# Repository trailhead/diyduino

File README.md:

# diyduino
Open source Arduino-compaitible using only through hole soldering

USB interface is provided by either a 6 pin FTDI, or CP2102 style adapter.  Pinouts are provided for each.

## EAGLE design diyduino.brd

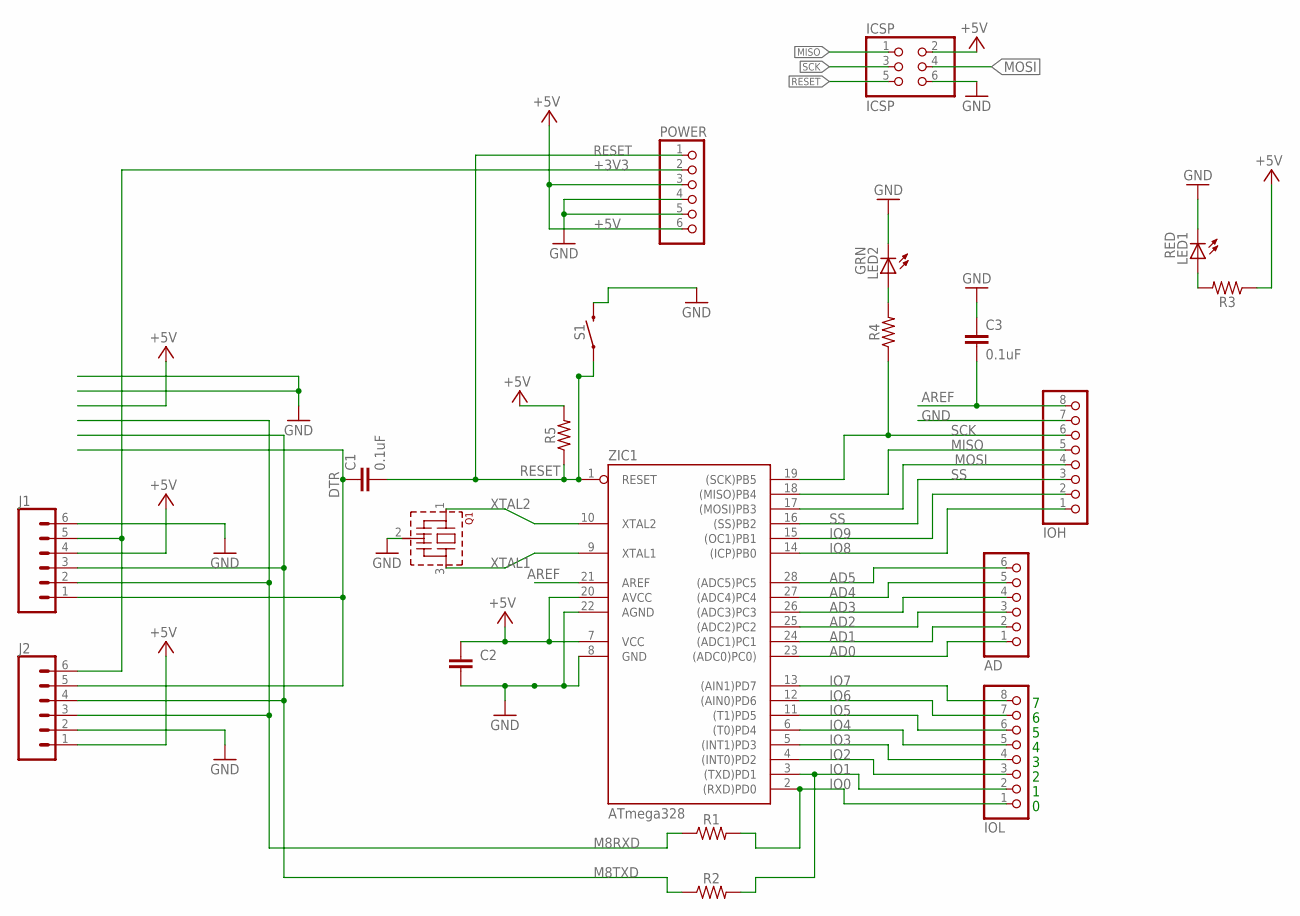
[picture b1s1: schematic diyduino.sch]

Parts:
AD: PINHD-1X6; 1X06
C1, C2, C3: 0.1uF; C2.5-2
ICSP: ICSP; 2X03
IOH: PINHD-1X8; 1X08
IOL: PINHD-1X8; 1X08
J1, J2: CONN_06SILK_FEMALE_PTH; 1X06
LED1: RED; LED3MM
LED2: GRN; LED3MM
POWER: PINHD-1X6; 1X06
Q1: CSTLS_X
R1, R2, R3, R4, R5: AXIAL-0.3
S1: MOMENTARY-SWITCH-SPST-PTH-6.0MM; TACTILE_SWITCH_PTH_6.0MM
ZIC1: ATmega328; DIL28-3

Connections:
+3V3: J1.5, J2.6, POWER.2
+5V: C2.2, ICSP.2, J1.4, J2.1, POWER.3, POWER.6, R3.P$1 (1), R5.P$2 (2), ZIC1.7 (VCC), ZIC1.20 (AVCC)
AD0: AD.1, ZIC1.23 ((ADC0)PC0))
AD1: AD.2, ZIC1.24 ((ADC1)PC1)
AD2: AD.3, ZIC1.25 ((ADC2)PC2)
AD3: AD.4, ZIC1.26 ((ADC3)PC3)
AD4: AD.5, ZIC1.27 ((ADC4)PC4)
AD5: AD.6, ZIC1.28 ((ADC5)PC5)
AREF: C3.2, IOH.8, ZIC1.21 (AREF)
DTR: C1.1, J1.1, J2.5
GND: C2.1, C3.1, ICSP.6, IOH.7, J1.6, J2.2, LED1.K (C), LED2.K (C), POWER.4, POWER.5, Q1.2 (VSS), S1.3 (2), ZIC1.8 (GND), ZIC1.22 (AGND)
IO0: IOL.1, R1.P$2 (2), ZIC1.2 ((RXD)PD0)
IO1: IOL.2, R2.P$2 (2), ZIC1.3 ((TXD)PD1)
IO2: IOL.3, ZIC1.4 ((INT0)PD2)
IO3: IOL.4, ZIC1.5 ((INT1)PD3)
IO4: IOL.5, ZIC1.6 ((T0)PD4)
IO5: IOL.6, ZIC1.11 ((T1)PD5)
IO6: IOL.7, ZIC1.12 ((AIN0)PD6)
IO7: IOL.8, ZIC1.13 ((AIN1)PD7)
IO8: IOH.1, ZIC1.14 ((ICP)PB0)
IO9: IOH.2, ZIC1.15 ((OC1)PB1)
M8RXD: J1.2, J2.3, R1.P$1 (1)
M8TXD: J1.3, J2.4, R2.P$1 (1)
MISO: ICSP.1, IOH.5, ZIC1.18 ((MISO)PB4)
MOSI: ICSP.4, IOH.4, ZIC1.17 ((MOSI)PB3)
unnamed: LED2.A, R4.P$2 (2)
unnamed: LED1.A, R3.P$2 (2)
RESET: C1.2, ICSP.5, POWER.1, R5.P$1 (1), S1.1, ZIC1.1 (RESET)
SCK: ICSP.3, IOH.6, R4.P$1 (1), ZIC1.19 ((SCK)PB5)
SS: IOH.3, ZIC1.16 ((SS)PB2)
XTAL1: Q1.3, ZIC1.9 (XTAL1)
XTAL2: Q1.1, ZIC1.10 (XTAL2)

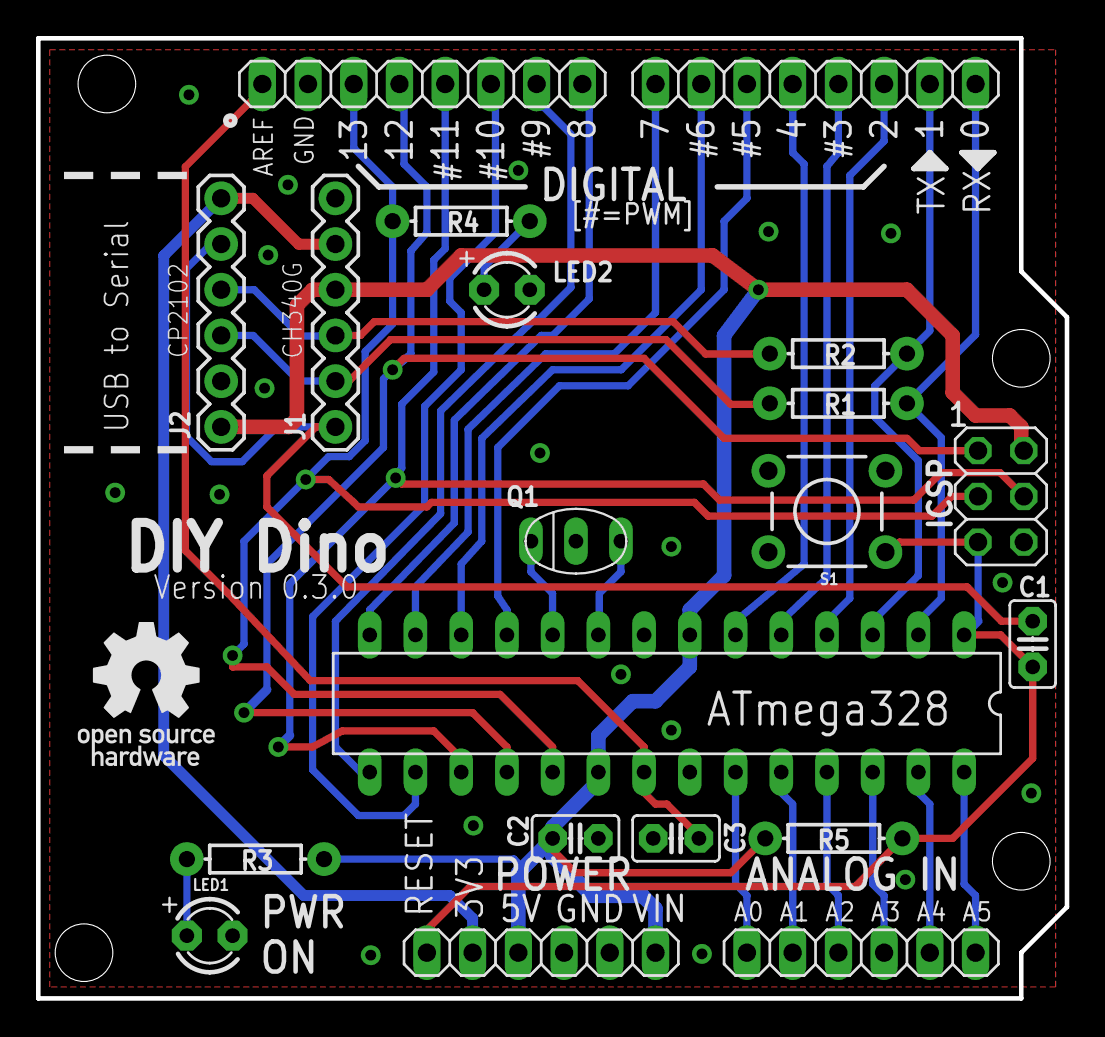
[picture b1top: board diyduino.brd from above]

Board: 2 copper layers, 57.1 x 53.3 mm, 20 parts (0 on the bottom side), 32 nets.

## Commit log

2018-05-09 initial eagle commit
2018-05-09 adding license badge
2018-05-09 adding USB info
2018-05-18 0.3.0 changes, fixed CH340 pinout, changed crystal to resonator
2018-05-18 adding dinosaur!

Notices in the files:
README.md:
License: CC BY-SA 4.0
diyduino.brd:
Users/chris/Downloads/cc-by-sa-bw.bmp
parts and their libraries:
SparkFun-Resistors: Licensing: Creative Commons ShareAlike 4.0 International - https://creativecommons.org/licenses/by-sa/4.0
